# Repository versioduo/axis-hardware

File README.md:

# axis-hardware

🧭 Orientation Sensor Controller

## Board

## Schematic

[PDF](axis.pdf)

## Bill Of Materials

[Interactive BOM](https://htmlpreview.github.io/?https://github.com/versioduo/axis-hardware/main/axis-bom.html)

## Software

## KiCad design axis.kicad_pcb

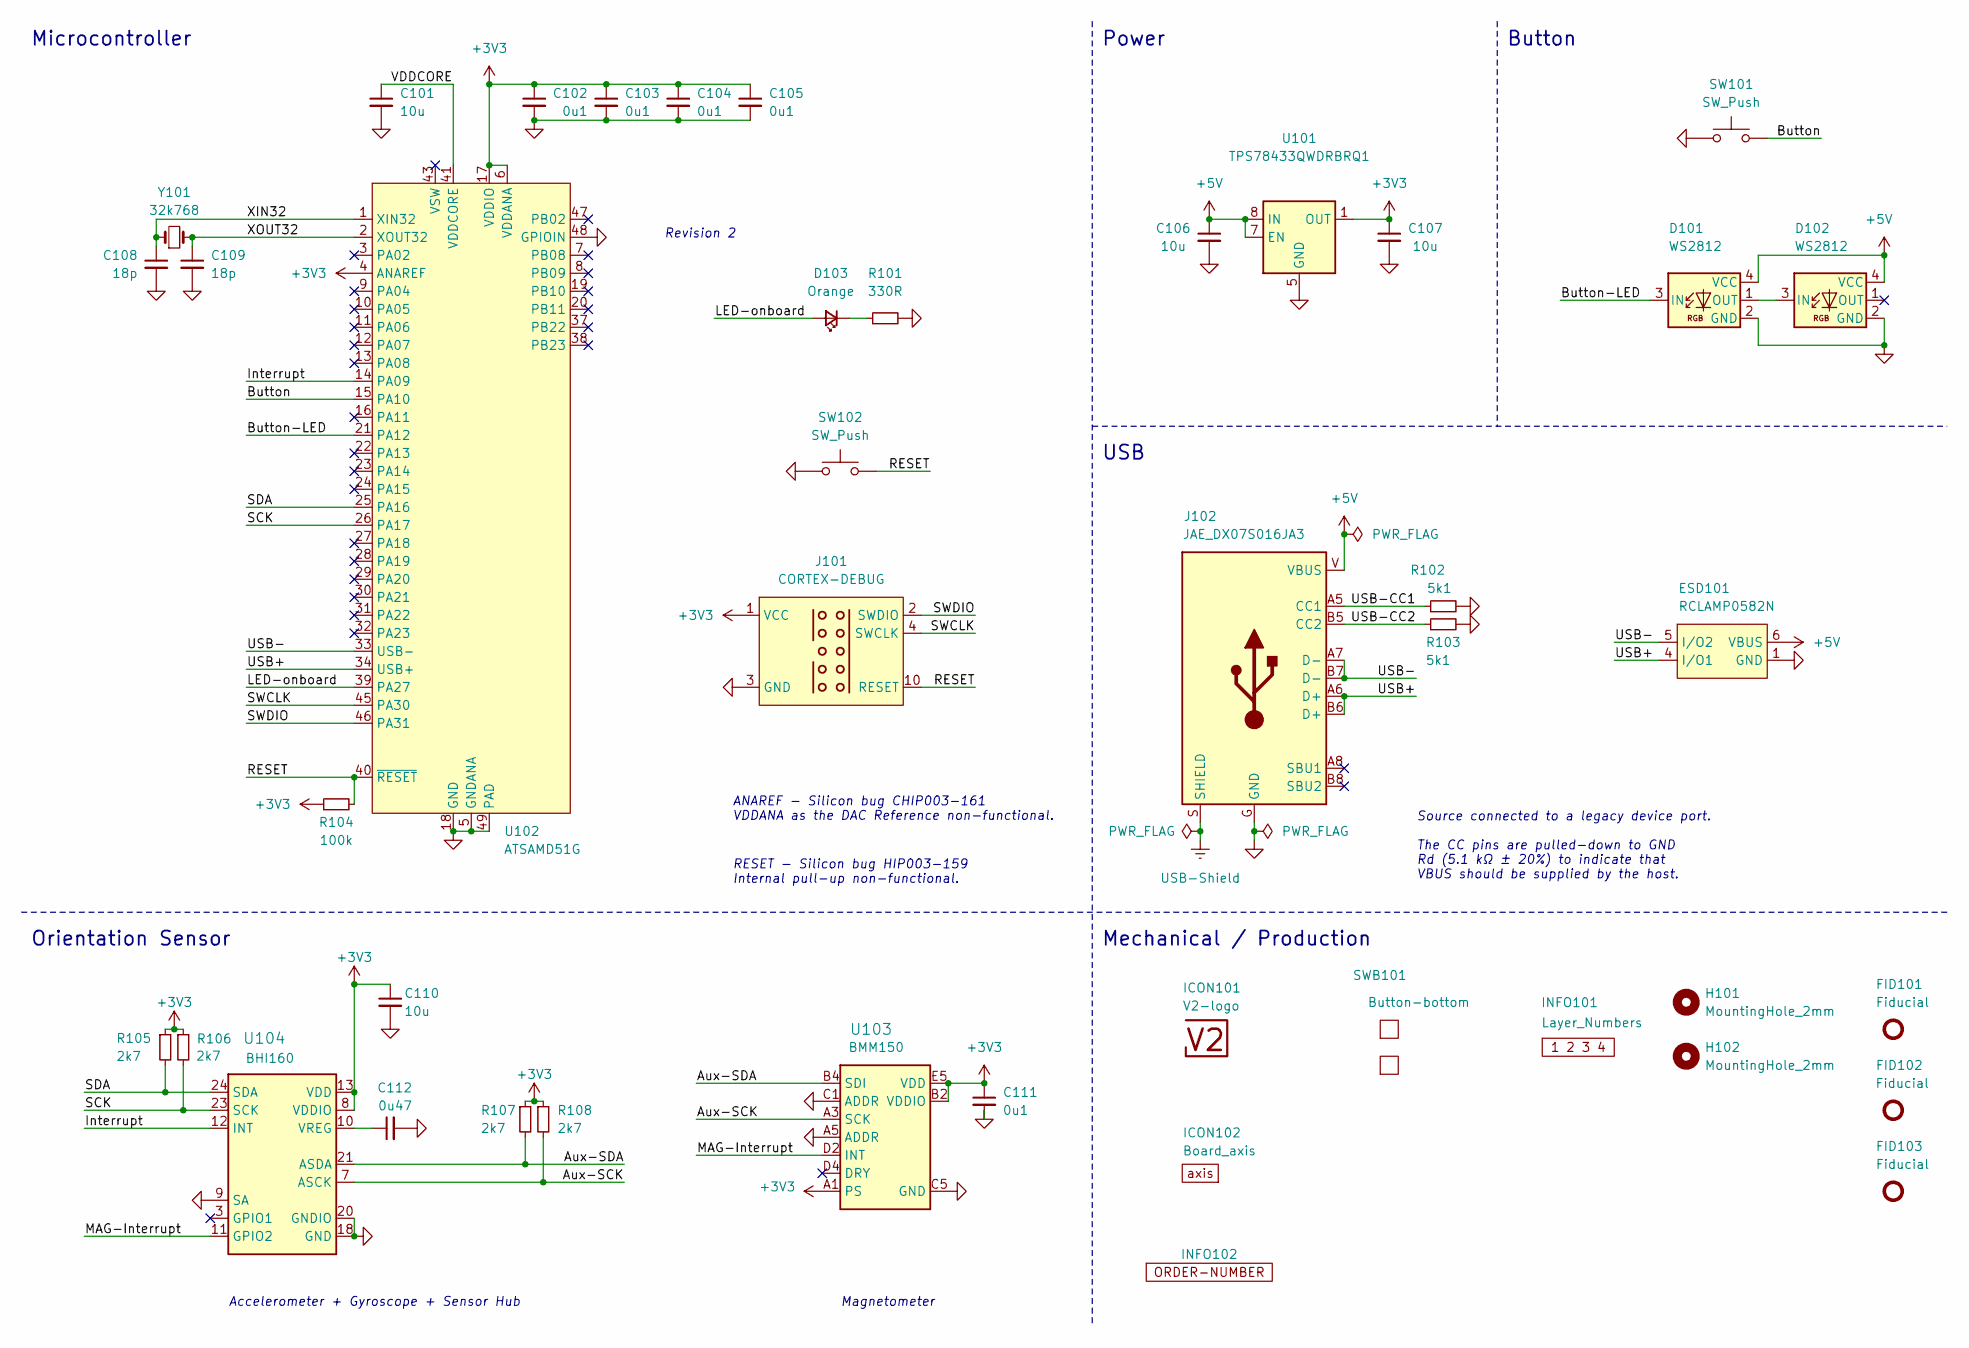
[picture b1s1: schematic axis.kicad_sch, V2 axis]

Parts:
C101, C110: 10u; C_0603_1608Metric
C102, C103, C104, C105, C111: 0u1; C_0603_1608Metric
C106, C107: 10u; C_0805_2012Metric
C108, C109: 18p; C_0603_1608Metric
C112: 0u47; C_0603_1608Metric
D101, D102: WS2812; WS2812-2020
D103: Orange; LED_0603_1608Metric
ESD101: RCLAMP0582N; SLP1210N6
FID101, FID102, FID103: Fiducial; Fiducial_0.5mm_Mask1mm_Paste
H101, H102: MountingHole_2mm
ICON101: V2-logo; Logo_Small
ICON102: Board_axis; Board_axis_Small
INFO101: Layer_Numbers
INFO102: ORDER-NUMBER; Order_Number
J101: CORTEX-DEBUG; Cortex_Debug_Pad
J102: JAE_DX07S016JA3
R101: 330R; R_0603_1608Metric
R102, R103: 5k1; R_0603_1608Metric
R104: 100k; R_0603_1608Metric
R105, R106, R107, R108: 2k7; R_0603_1608Metric
SW101, SW102: SW_Push; SKSG
SWB101: Button-bottom; PCB_Button-bottom
U101: TPS78433QWDRBRQ1; VSON-8-1_3x3mm_P0.65_EP1.65x2.4mm
U102: ATSAMD51G; QFN-48-1EP_7x7mm_P0.5mm_EP5.45x5.45mm_ThermalVias
U103: BMM150; WLCSP-1.56x1.56
U104: BHI160; LGA24-3x3
Y101: 32k768; Crystal_SMD_3215-2Pin_3.2x1.5mm

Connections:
+3V3: C102.1, C103.1, C104.1, C105.1, C107.1, C110.1, C111.1, J101.1 (VCC), R104.1, R105.1, R106.1, R107.1, R108.1, U101.1 (OUT), U102.4 (ANAREF), U102.6 (VDDANA), U102.17 (VDDIO), U102.36 (VDDIO), U102.44 (VDDIO), U103.A1 (PS), U103.B2 (VDDIO), U103.E5 (VDD), U104.8 (VDDIO), U104.13 (VDD)
+5V: C106.1, D101.4 (VCC), D102.4 (VCC), ESD101.6 (VBUS), J102.V (VBUS), U101.7 (EN), U101.8 (IN)
/Aux-SCK: R108.2, U103.A3 (SCK), U104.7 (ASCK)
/Aux-SDA: R107.2, U103.B4 (SDI), U104.21 (ASDA)
/Button: SW101.2, U102.15 (PA10)
/Button-LED: D101.3 (IN), U102.21 (PA12)
/Interrupt: U102.14 (PA09), U104.12 (INT)
/LED-onboard: D103.2 (A), U102.39 (PA27)
/MAG-Interrupt: U103.D2 (INT), U104.11 (GPIO2)
/RESET: J101.10 (RESET), R104.2, SW102.2, U102.40 (~RESET)
/SCK: R106.2, U102.26 (PA17), U104.23 (SCK)
/SDA: R105.2, U102.25 (PA16), U104.24 (SDA)
/SWCLK: J101.4 (SWCLK), U102.45 (PA30)
/SWDIO: J101.2 (SWDIO), U102.46 (PA31)
/USB+: ESD101.4 (I/O1), J102.A6 (D+), J102.B6 (D+), U102.34 (USB+)
/USB-: ESD101.5 (I/O2), J102.A7 (D-), J102.B7 (D-), U102.33 (USB-)
/USB-CC1: J102.A5 (CC1), R102.1
/USB-CC2: J102.B5 (CC2), R103.1
/VDDCORE: C101.1, U102.41 (VDDCORE)
/XIN32: C108.1, U102.1 (XIN32), Y101.1
/XOUT32: C109.1, U102.2 (XOUT32), Y101.2
GND: C101.2, C102.2, C103.2, C104.2, C105.2, C106.2, C107.2, C108.2, C109.2, C110.2, C111.2, C112.2, D101.2 (GND), D102.2 (GND), ESD101.1 (GND), J101.3 (GND), J101.5 (GND), J102.G (GND), R101.2, R102.2, R103.2, SW101.1, SW102.1, U101.5 (GND), U101.9 (GND), U102.5 (GNDANA), U102.18 (GND), U102.35 (GND), U102.42 (GND), U102.48 (PB03), U102.49 (PAD), U103.A5 (ADDR), U103.C1 (ADDR), U103.C5 (GND), U103.E1 (GND), U103.E3 (GND), U104.9 (SA), U104.18 (GND), U104.20 (GNDIO)
unnamed: D101.1 (OUT), D102.3 (IN)
unnamed: D103.1 (K), R101.1
unnamed: C112.1, U104.10 (VREG)
USB-Shield: J102.S (SHIELD)

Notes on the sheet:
﻿ANAREF - Silicon bug CHIP003-161 VDDANA as the DAC Reference non-functional.
RESET - ﻿Silicon bug HIP003-159 Internal pull-up non-functional.
﻿Source connected to a legacy device port. The CC pins are pulled-down to GND Rd (5.1 kΩ ± 20%) to indicate that VBUS should be supplied by the host.
Button
Revision 2
Mechanical / Production
Magnetometer
Power
Accelerometer + Gyroscope + Sensor Hub
Microcontroller
USB
Orientation Sensor

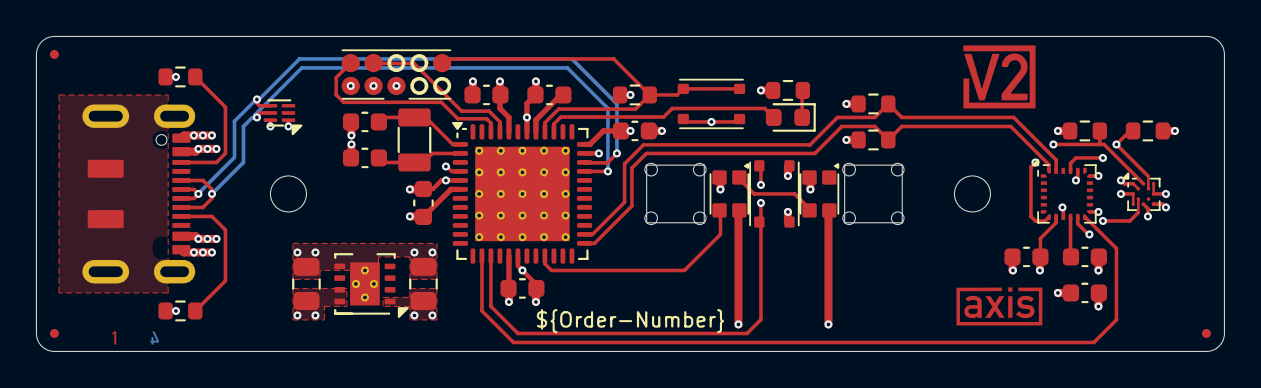
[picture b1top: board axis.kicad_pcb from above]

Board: 4 copper layers, 66.0 x 17.5 mm, 43 parts (0 on the bottom side), 25 nets.

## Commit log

2023-01-05 Import
2023-08-28 Refresh
2024-03-28 Update to Kicad 8
2025-10-26 Replace LDO
2025-10-30 GND label
2025-11-02 Replace standoffs
2025-11-15 Add front + back
2025-11-16 Change capacitors
2025-11-28 Colours
2025-12-01 Fix front
2025-12-12 Remove revision pin
